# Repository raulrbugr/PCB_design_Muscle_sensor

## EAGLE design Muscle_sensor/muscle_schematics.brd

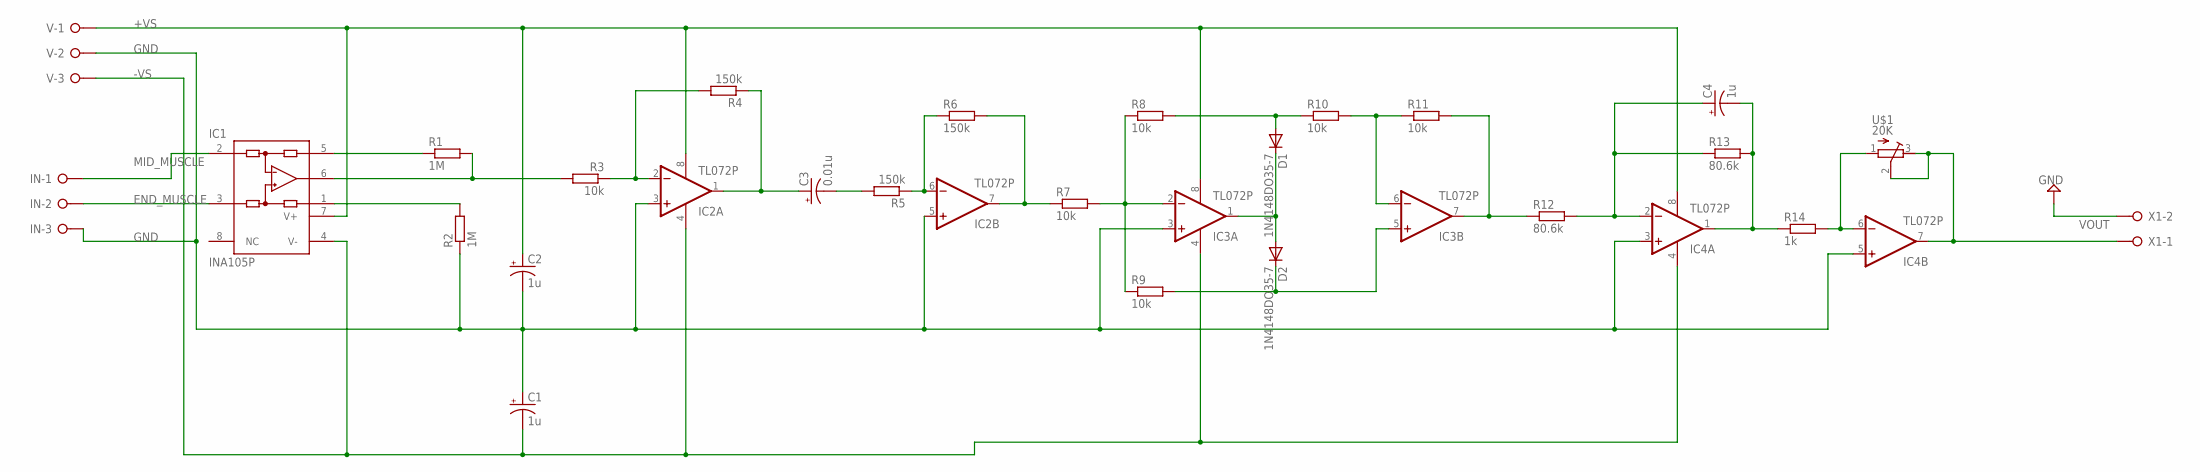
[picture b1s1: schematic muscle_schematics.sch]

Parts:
C1, C2, C4: 1u; E5-6
C3: 0.01u; E5-6
D1, D2: 1N4148DO35-7; DO35-7
IC1: INA105P; DIL08
IC2, IC3, IC4: TL072P; DIL08
IN: W237-3E
R1, R2: 1M; 0207/10
R3, R7, R8, R9, R10, R11: 10k; 0207/10
R4, R5, R6: 150k; 0207/10
R12, R13: 80.6k; 0207/10
R14: 1k; 0207/10
U$1: 20K; RTRIM3339P
V: W237-3E
X1: W237-02P; W237-132

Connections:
+VS: C2.+, IC1.7 (V+), IC2.8 (V+), IC3.8 (V+), IC4.8 (V+), V.1
-VS: C1.-, IC1.4 (V-), IC2.4 (V-), IC3.4 (V-), IC4.4 (V-), V.3
END_MUSCLE: IC1.3 (+IN), IN.2
GND: C1.+, C2.-, IC2.3 (+IN), IC2.5 (+IN), IC3.3 (+IN), IC4.3 (+IN), IC4.5 (+IN), IN.3, R2.1, V.2, X1.2
MID_MUSCLE: IC1.2 (-IN), IN.1
unnamed: IC1.5 (SENSE), R1.1
unnamed: IC1.6 (OUT), R1.2, R3.2
unnamed: IC1.1 (REF), R2.2
unnamed: C3.+, IC2.1 (OUT), R4.1
unnamed: C3.-, R5.2
unnamed: IC2.2 (-IN), R3.1, R4.2
unnamed: IC2.6 (-IN), R5.1, R6.1
unnamed: IC3.6 (-IN), R10.2, R11.1
unnamed: IC3.2 (-IN), R7.2, R8.1, R9.1
unnamed: D1.A, R8.2, R10.1
unnamed: D2.C, IC3.5 (+IN), R9.2
unnamed: IC2.7 (OUT), R6.2, R7.1
unnamed: IC3.7 (OUT), R11.2, R12.1
unnamed: D1.C, D2.A, IC3.1 (OUT)
unnamed: C4.+, IC4.2 (-IN), R12.2, R13.1
unnamed: IC4.6 (-IN), R14.2, U$1.1 (A)
unnamed: C4.-, IC4.1 (OUT), R13.2, R14.1
VOUT: IC4.7 (OUT), U$1.2 (S), U$1.3 (E), X1.1

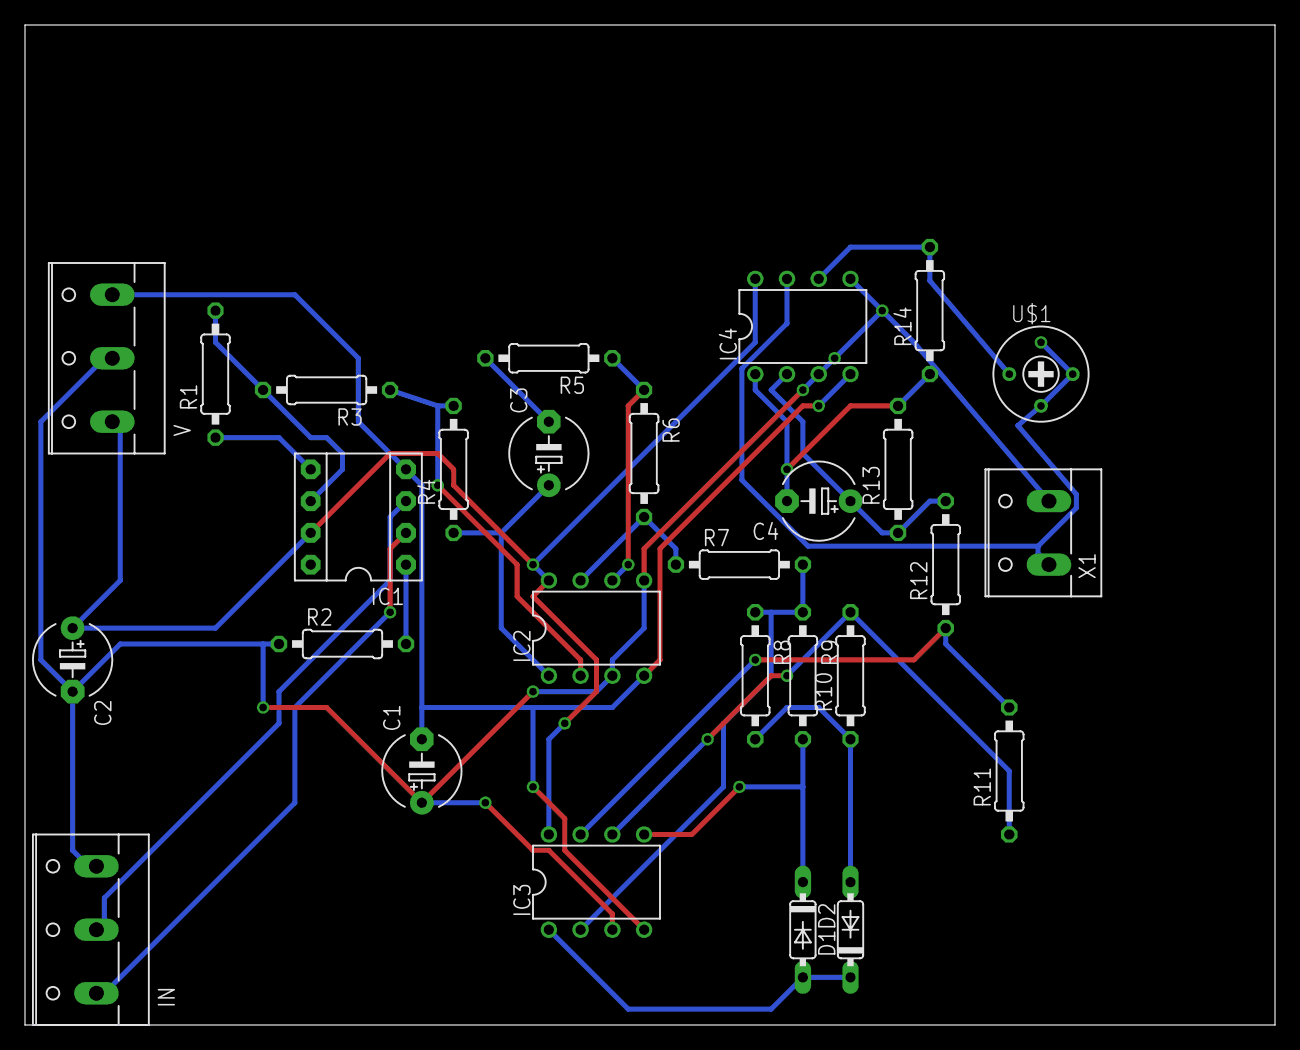
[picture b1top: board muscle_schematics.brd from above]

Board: 2 copper layers, 100.0 x 80.0 mm, 28 parts (0 on the bottom side), 23 nets.

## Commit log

2017-05-02 :tada: Added .gitattributes & .gitignore files
2017-05-02 Muscle sensor PCB
